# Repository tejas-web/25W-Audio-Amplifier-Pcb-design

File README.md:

# 25W Audio Amplifier Pcb design

Revision 2 of a mono TDA2050 audio amplifier designed in **KiCad 9**, with a two-layer PCB,
schematic, SPICE experiments, and audio-file input/output waveform results.
The 25W project title does not represent a verified output power for this board.

**Status: design and simulation prototype.** The saved design has a reversed
negative-rail capacitor (C4): correct its polarity before fabrication or power-up.
See [design review](simulation/PCB-before-ordering.md) for the other open items.
The simulation uses an educational behavioural model; results are not measured
hardware specifications or a manufacturer-validated TDA2050 simulation.

## PCB and schematic

| Top copper and silkscreen | Bottom copper (mirrored) |
| --- | --- |
|  |  |

[Schematic PDF](docs/previews/schematic.pdf) · [KiCad schematic](25W-Audio-Amplifier-Pcb-design.kicad_sch) ·
[KiCad PCB](25W-Audio-Amplifier-Pcb-design.kicad_pcb) · [Project settings](25W-Audio-Amplifier-Pcb-design.kicad_pro)

## Design specifications

| Parameter | Saved design / simulation setting |
| --- | --- |
| Amplifier | TDA2050, mono, noninverting configuration |
| Supply | Split +12 V / GND / −12 V used in simulation |
| PCB dimensions | 60 × 35 mm |
| Copper layers | 2: F.Cu and B.Cu |
| Nominal board thickness | 1.6 mm |
| Assembly | Through-hole components |
| Supply / principal output trace width | 1.5 mm; no current rating established |
| Feedback resistors | R3 = 22 kΩ, R2 = 680 Ω |
| Nominal midband feedback gain | 1 + 22000/680 ≈ 33.35 V/V (30.46 dB) |
| Input coupling / input resistance | C1 = 1 µF / R1 = 22 kΩ |
| Feedback capacitor | C2 = 22 µF |
| Supply bypass | C3, C6 = 100 nF; C4, C7 = 220 µF |
| Output series RC network | R4 = 4.7 Ω, C5 = 100 nF |
| Simulated loads | 4 Ω and 8 Ω resistors |
| Validated hardware power / bandwidth / THD | Not measured or established |

### Connections

| Connector | Pin assignments |
| --- | --- |
| J2 — audio input | 1: GND; 2: audio signal (currently mislabeled `+5V`) |
| J1 — speaker/load output | 1: amplifier output; 2: GND |
| J4 — split supply | 1: +12 V; 2: GND; 3: −12 V |

The `+5V` net label on J2 is the audio input in this project, not a simulated
5 V supply. U1 pins are 1: noninverting input, 2: inverting input, 3: negative
supply, 4: output, 5: positive supply.

### Components

| Reference | Value / part | Role |
| --- | --- | --- |
| U1 | TDA2050 | Power amplifier |
| R1 | 22 kΩ | Input bias return |
| R2 | 680 Ω | Feedback ground leg |
| R3 | 22 kΩ | Output feedback |
| R4 | 4.7 Ω | Output RC network resistor |
| C1 | 1 µF | Input coupling |
| C2 | 22 µF | Feedback DC blocking |
| C3, C6 | 100 nF | Supply bypass |
| C4, C7 | 220 µF | Supply bulk decoupling |
| C5 | 100 nF | Output RC network capacitor |
| J1, J2 | 2-pin, 5 mm pitch terminal blocks | Output and input |
| J4 | 3-pin, 5 mm pitch terminal block | Split supply |

[Full BOM with assigned footprints](docs/BOM.csv). Voltage ratings, resistor
power ratings and the exact U1 package fit still need verification; the BOM
records the saved design rather than a purchasing specification.

## Simulation results

### Sine-wave tests

At 1 kHz and 0.1 V peak input:

| Load | Gain | Output peak | Output RMS | Mean load power |
| --- | --- | --- | --- | --- |
| 8 Ω | 33.339 V/V | 3.335 V | 2.357 V | 0.695 W |
| 4 Ω | 33.339 V/V | 3.335 V | 2.357 V | 1.389 W |

The repository also includes 0.5 V peak overdrive tests. Their clipped waveform
power is not a clean rated output-power specification. Raw results are in
[results.json](simulation/results.json) and the `*_ac.txt`, `*_tran.txt` and
`*_op.txt` files.

### Synthetic audio input

The audio runner also includes a [synthetic 1 kHz input/output example](simulation/audio_demo/waveforms.png).
The plotted output is a model result with an 8 Ω resistive load.

### Reproduce

Open `25W-Audio-Amplifier-Pcb-design.kicad_pro` in KiCad 9 with the standard symbol and footprint
libraries. For simulations, use Python 3 with NumPy, SciPy, Matplotlib and the
ngspice shared library (`libngspice.so.0` on the tested Linux system).

```sh
PYTHONNOUSERSITE=1 MPLCONFIGDIR=/tmp/pcb-simulation-mpl python3 simulation/run_simulation.py
```

For your own WAV recording:

```sh
PYTHONNOUSERSITE=1 python3 simulation/audio_simulation.py /path/to/audio.wav --start 0 --duration 1 --input-peak 0.1 --load 8 --out simulation/my_audio_results
```

Long audio runs can be slow. PCM and floating-point WAV are supported; convert
other formats to WAV before running. See [simulation instructions](simulation/README.md)
for netlist refresh and interactive KiCad setup. The audio runner reads the saved
`small_8ohm.cir` connectivity, so regenerate it after relevant schematic changes.

## Model limitations and open design work

The behavioural amplifier has 100,000 V/V small-signal open-loop gain, a fixed
approximately ±10 V smooth limiter and 0.1 Ω output resistance. It does not model
frequency compensation, slew rate, current protection, noise, thermal behaviour
or PCB parasitics. Changing supply voltages does not change its limiter.
It cannot establish real stability, safe maximum power or heatsink requirements.

Before building, resolve the items documented in [PCB-before-ordering.md](simulation/PCB-before-ordering.md):

- Reverse C4's design polarity so its positive terminal faces ground and its
  negative terminal faces −12 V, including PCB markings.
- Rename the audio input net and verify component ratings and the exact U1
  footprint against the purchased part.
- Review the output RC network, bypass placement, high-current ground returns
  and heatsink arrangement.
- Synchronize schematic/PCB values, refill zones and repeat ERC/DRC.

KiCad 9.0.9 checks on the saved revision 2 design found zero schematic ERC
violations and zero unconnected pads. PCB DRC reported three silkscreen overlap
warnings. The schematic-to-PCB comparison reported five warnings: two pad net
mismatches involving `IN` and `+5V`, and three connector value mismatches.
See the [ERC report](docs/checks/tda2050-erc.rpt) and
[DRC report](docs/checks/tda2050-drc.rpt). Fabrication exports are pending the
C4 polarity correction and layout review.

## Repository contents

| Path | Contents |
| --- | --- |
| `25W-Audio-Amplifier-Pcb-design.kicad_pro`, `.kicad_sch`, `.kicad_pcb` | Main editable KiCad design |
| `docs/` | Preview exports, schematic PDF and BOM |
| `simulation/` | Python runners, model, netlist, SPICE decks, plots, audio and raw data |
| `gnd-via-example/` | Separate ground-stitching PCB example, preview and DRC report |
| `25W-Audio-Amplifier-Pcb-design.wbk` | KiCad simulation workbook with operating-point setup |

Transient editor locks, local preferences and footprint caches are excluded.
The KiCad files are from the saved revision 2 design.

## Attribution and licensing

No project license has been selected.

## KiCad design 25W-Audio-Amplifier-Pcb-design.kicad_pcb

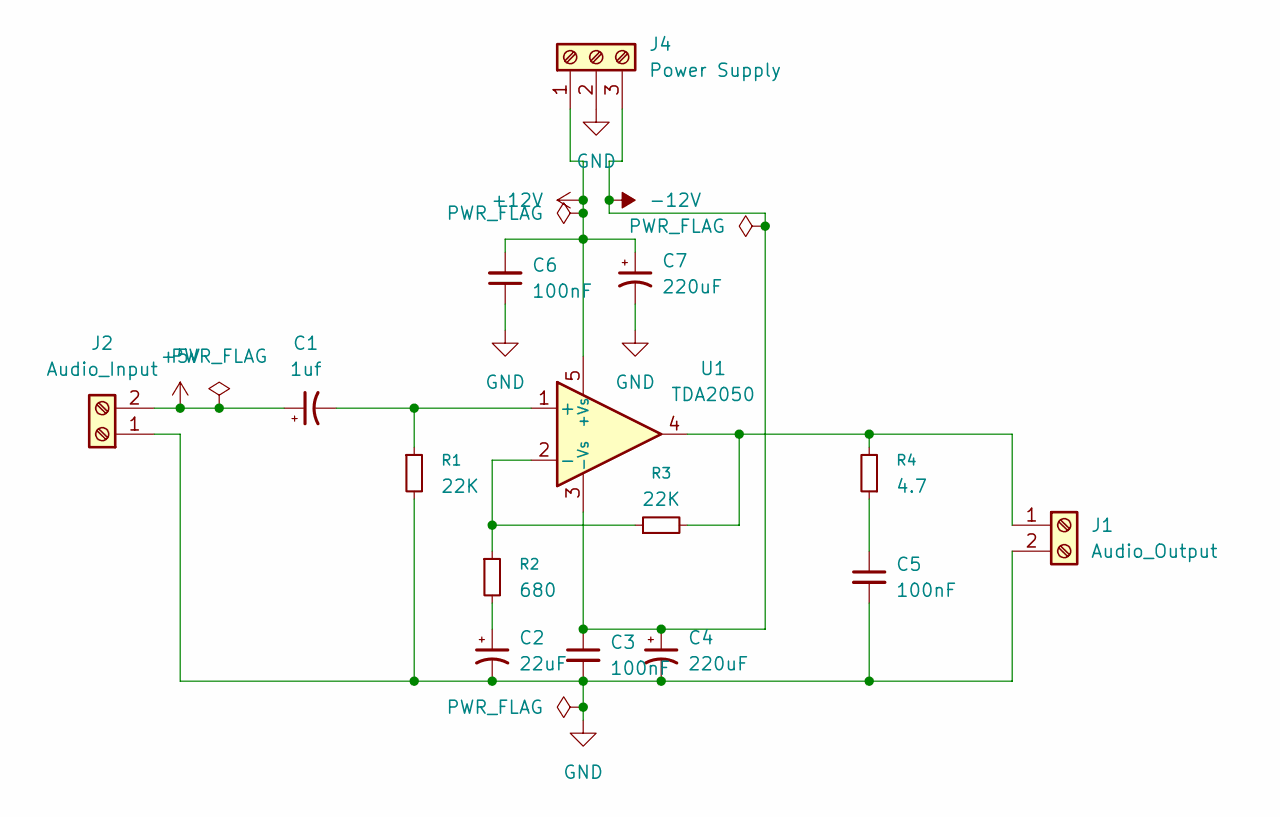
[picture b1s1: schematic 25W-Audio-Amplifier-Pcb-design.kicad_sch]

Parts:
C1: 1uf; CP_Radial_D5.0mm_P2.00mm
C2: 22uF; CP_Radial_D5.0mm_P2.00mm
C3, C5, C6: 100nF; C_Disc_D5.0mm_W2.5mm_P5.00mm
C4, C7: 220uF; CP_Radial_D8.0mm_P3.50mm
J1: Audio_Output; TerminalBlock_Phoenix_MKDS-1,5-2_1x02_P5.00mm_Horizontal
J2: Audio_Input; TerminalBlock_Phoenix_MKDS-1,5-2_1x02_P5.00mm_Horizontal
J4: Power Supply; TerminalBlock_Phoenix_MKDS-1,5-3_1x03_P5.00mm_Horizontal
R1, R3: 22K; R_Axial_DIN0207_L6.3mm_D2.5mm_P7.62mm_Horizontal
R2: 680; R_Axial_DIN0207_L6.3mm_D2.5mm_P7.62mm_Horizontal
R4: 4.7; R_Axial_DIN0207_L6.3mm_D2.5mm_P7.62mm_Horizontal
U1: TDA2050; TO-220-5_P3.4x3.7mm_StaggerOdd_Lead3.8mm_Vertical

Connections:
+12V: C6.2, C7.1, J4.1, U1.5 (+Vs)
-12V: C3.1, C4.1, J4.3, U1.3 (-Vs)
GND: C2.2, C3.2, C4.2, C5.2, C6.1, C7.2, J1.2, J2.1, J4.2, R1.2
IN: C1.1, J2.2
unnamed: C2.1, R2.2
unnamed: C5.1, R4.1
unnamed: J1.1, R3.2, R4.2, U1.4
unnamed: C1.2, R1.1, U1.1 (+)
unnamed: R2.1, R3.1, U1.2 (-)

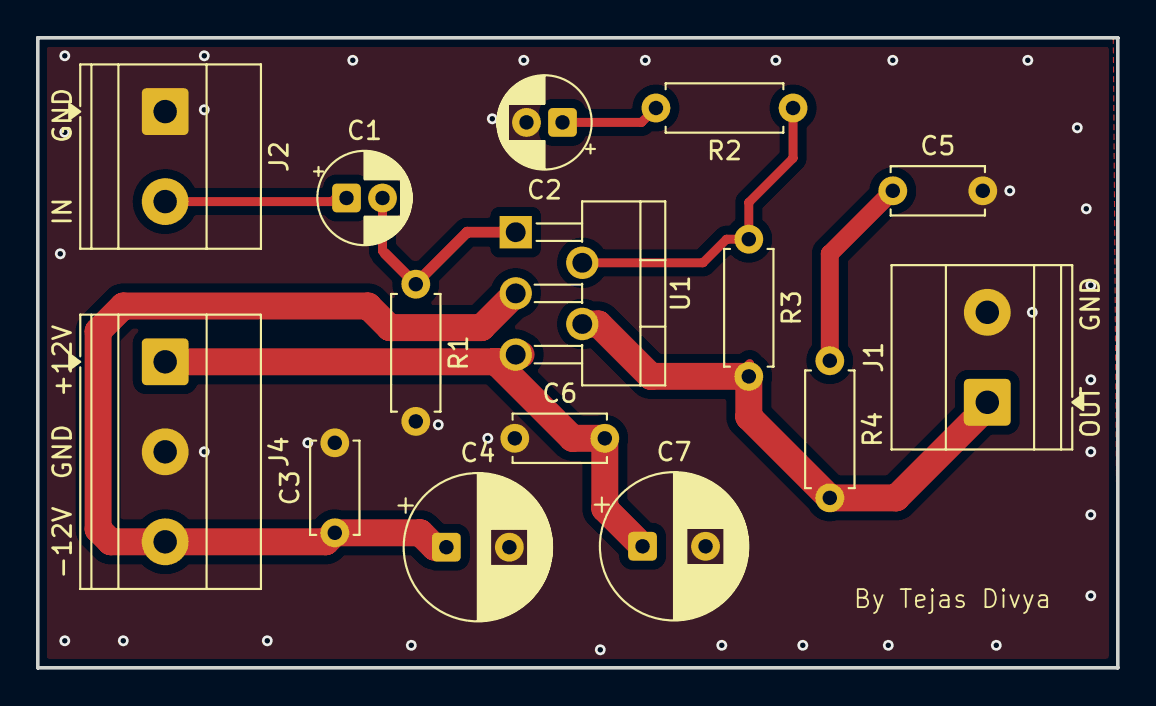
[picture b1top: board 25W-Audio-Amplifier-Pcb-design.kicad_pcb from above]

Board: 2 copper layers, 60.0 x 35.0 mm, 15 parts (0 on the bottom side), 9 nets.
